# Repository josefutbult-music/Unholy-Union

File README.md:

# Unholy Union
A microphone preamp made for integrating effect pedals to a microphone signal-chain

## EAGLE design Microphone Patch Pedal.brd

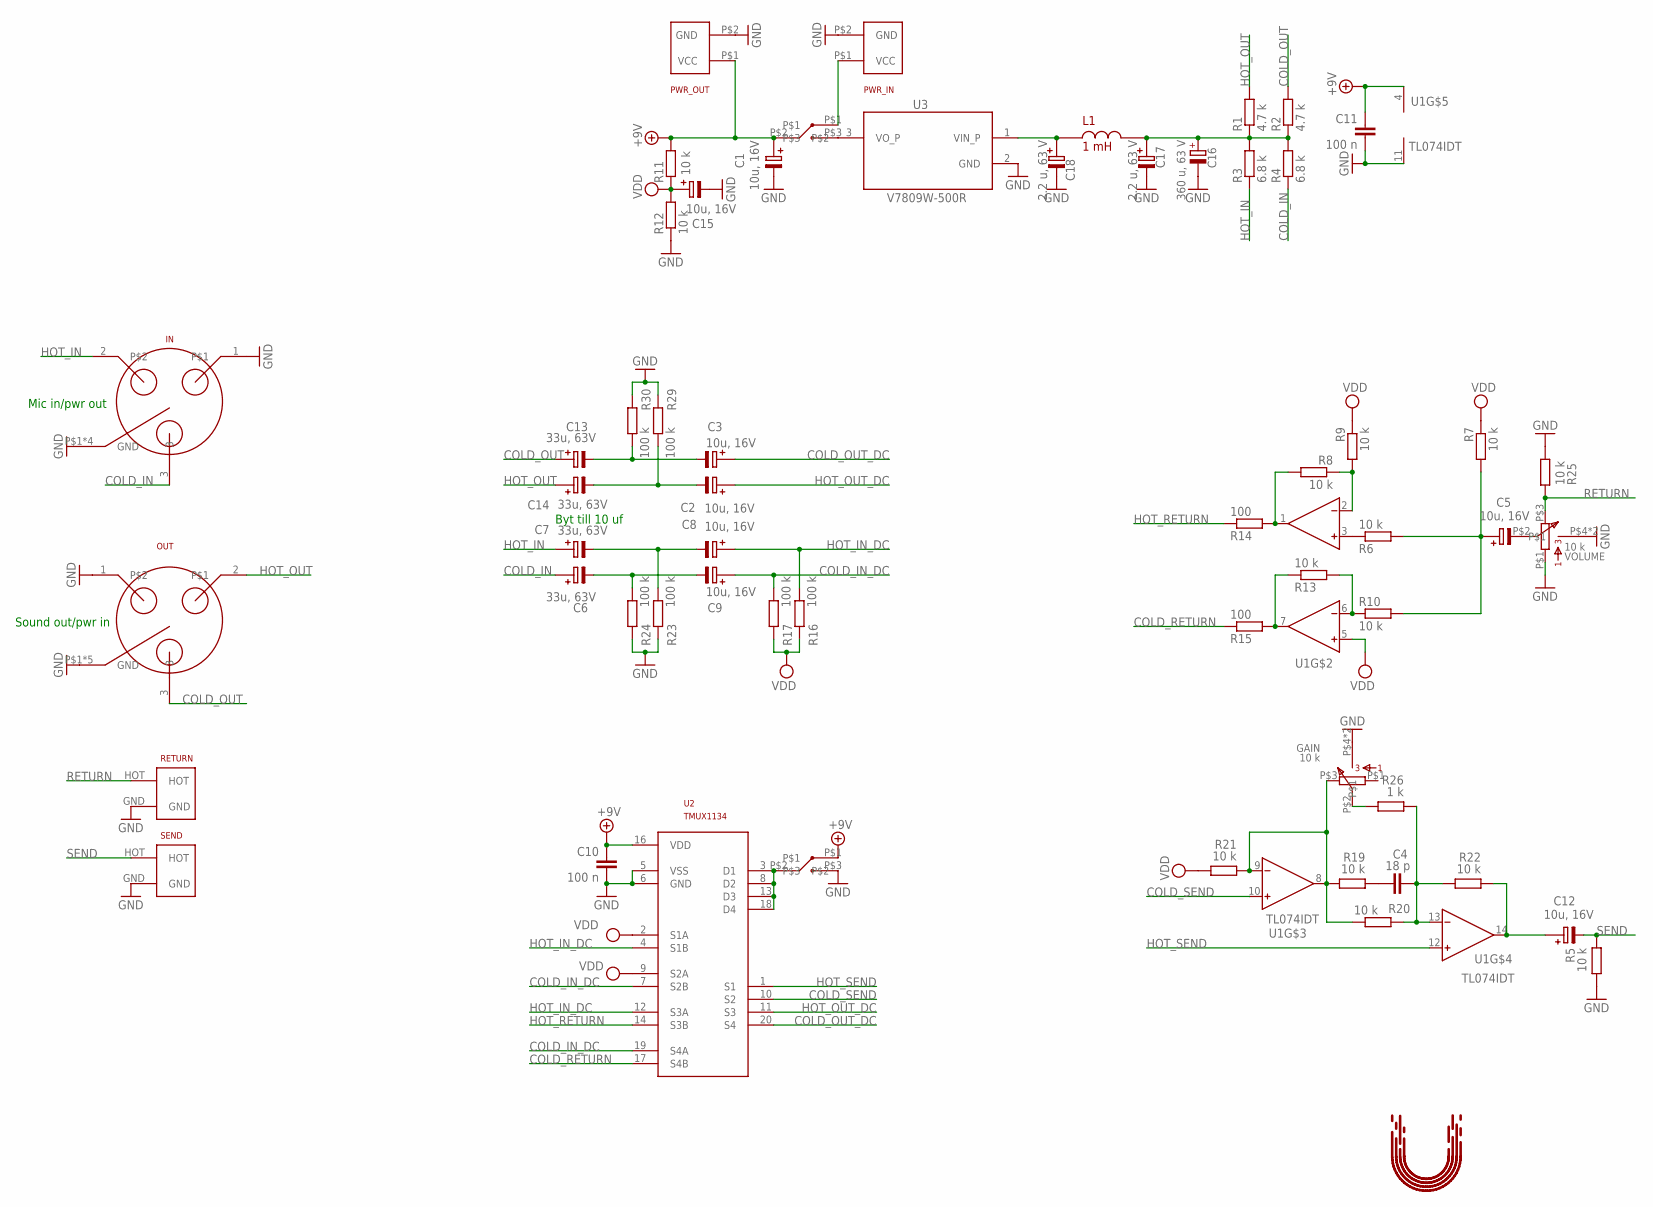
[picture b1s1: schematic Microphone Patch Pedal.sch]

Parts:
BYPASS: BUTTON; 3-HOLES
C1, C2, C3, C5, C8, C9, C12, C15: 10u, 16V; SV-A
C4: 18 p; C0603
C6, C7, C13, C14: 33u, 63V; SV-E/F
C10, C11: 100 n; C0603
C16: 360 u, 63 V; PANASONIC_FK_V_H; MPN UCM1J361MNJ1MS
C17, C18: 2.2 u, 63 V; SV-B; MPN EMVA630ADA2R2MD55G
GAIN: 10 k; RK09L1140
IN: XLR_FEMALE; NC3FAH2-S
L1: 1 mH; R3225
OUT: XLR_MALE; NC3MAH-S
PWR_IN: PWR
PWR_OUT: PWR
R1, R2: 4.7 k; R0603
R3, R4: 6.8 k; R0603
R5, R6, R7, R8, R9, R10, R11, R12, R13, R19, R20, R21, R22, R25: 10 k; R0603
R14, R15: 100; R0603
R16, R17, R23, R24, R29, R30: 100 k; R0603
R26: 1 k; R0603
RETURN: UNBALANCED_INPUT_JACK; BALANCED_INPUT_JACK
SEND: UNBALANCED_INPUT_JACK; BALANCED_INPUT_JACK
SWITCH: BUTTON; 3-HOLES
U1: TL074IDT; SOIC127P600X175-14N
U2: TMUX1134; SOP65P640X120-20N
U3: V7809W-500R; CONV_V7809W-500R
U$1: UTBULT_DESIGN4; UD_4
VOLUME: 10 k; RK09L1140

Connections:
+9V: BYPASS.P$1, C1.+, C10.1, C11.1, PWR_OUT.P$1 (VCC), R11.2, SWITCH.P$2, U1.4 (V+), U2.16 (VDD)
COLD_IN: C6.+, IN.3, R4.1
COLD_IN_DC: C9.+, R17.2, U2.7 (S2B), U2.19 (S4A)
COLD_OUT: C13.+, OUT.3, R2.2
COLD_OUT_DC: C3.+, U2.20 (S4)
COLD_RETURN: R15.1, U2.17 (S4B)
COLD_SEND: U1.10 (IN+), U2.10 (S2)
GND: BYPASS.P$3, C1.-, C10.2, C11.2, C15.-, C16.-, C17.-, C18.-, GAIN.P$4, GAIN.P$5, IN.1, IN.P$1 (GND), IN.P$2 (GND), IN.P$3 (GND), IN.P$6 (GND), OUT.1, OUT.P$1 (GND), OUT.P$2 (GND), OUT.P$3 (GND), OUT.P$4 (GND), OUT.P$5 (GND), PWR_IN.P$2 (GND), PWR_OUT.P$2 (GND), R5.2, R12.1, R23.1, R24.1, R25.2, R29.1, R30.1, RETURN.GND, SEND.GND, U1.11 (V-), U2.5 (VSS), U2.6 (GND), U3.2 (GND), VOLUME.P$1 (1), VOLUME.P$4, VOLUME.P$5
HOT_IN: C7.+, IN.2, R3.1
HOT_IN_DC: C8.+, R16.2, U2.4 (S1B), U2.12 (S3A)
HOT_OUT: C14.+, OUT.2, R1.2
HOT_OUT_DC: C2.+, U2.11 (S3)
HOT_RETURN: R14.1, U2.14 (S3B)
HOT_SEND: U1.12 (IN+), U2.1 (S1)
unnamed: R6.1, U1.3 (IN+)
unnamed: R8.2, R14.2, U1.1 (OUT)
unnamed: R8.1, R9.2, U1.2 (IN-)
unnamed: R10.1, R13.2, U1.6 (IN-)
unnamed: R13.1, R15.2, U1.7 (OUT)
unnamed: C5.-, VOLUME.P$2 (2)
unnamed: C16.+, C17.+, L1.2, R1.1, R2.1, R3.2, R4.2
unnamed: GAIN.P$3 (3), R19.2, R20.2, R21.1, U1.8 (OUT), U1.9 (IN-)
unnamed: SWITCH.P$3, U3.3 (VO_P)
unnamed: C4.1, R19.1
unnamed: C4.2, R20.1, R22.2, R26.1, U1.13 (IN-)
unnamed: C12.+, R22.1, U1.14 (OUT)
unnamed: C7.-, C8.-, R23.2
unnamed: C6.-, C9.-, R24.2
unnamed: C18.+, L1.1, U3.1 (VIN_P)
unnamed: GAIN.P$2 (2), R26.2
unnamed: C2.-, C14.-, R29.2
unnamed: C3.-, C13.-, R30.2
unnamed: C5.+, R6.2, R7.2, R10.2
unnamed: PWR_IN.P$1 (VCC), SWITCH.P$1
RETURN: R25.1, RETURN.HOT, VOLUME.P$3 (3)
SELECTOR: BYPASS.P$2, U2.3 (D1), U2.8 (D2), U2.13 (D3), U2.18 (D4)
SEND: C12.-, R5.1, SEND.HOT
VDD: C15.+, R7.1, R9.1, R11.1, R12.2, R16.1, R17.1, R21.2, U1.5 (IN+), U2.2 (S1A), U2.9 (S2A)

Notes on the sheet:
Mic in/pwr out
Sound out/pwr in
Byt till 10 uf

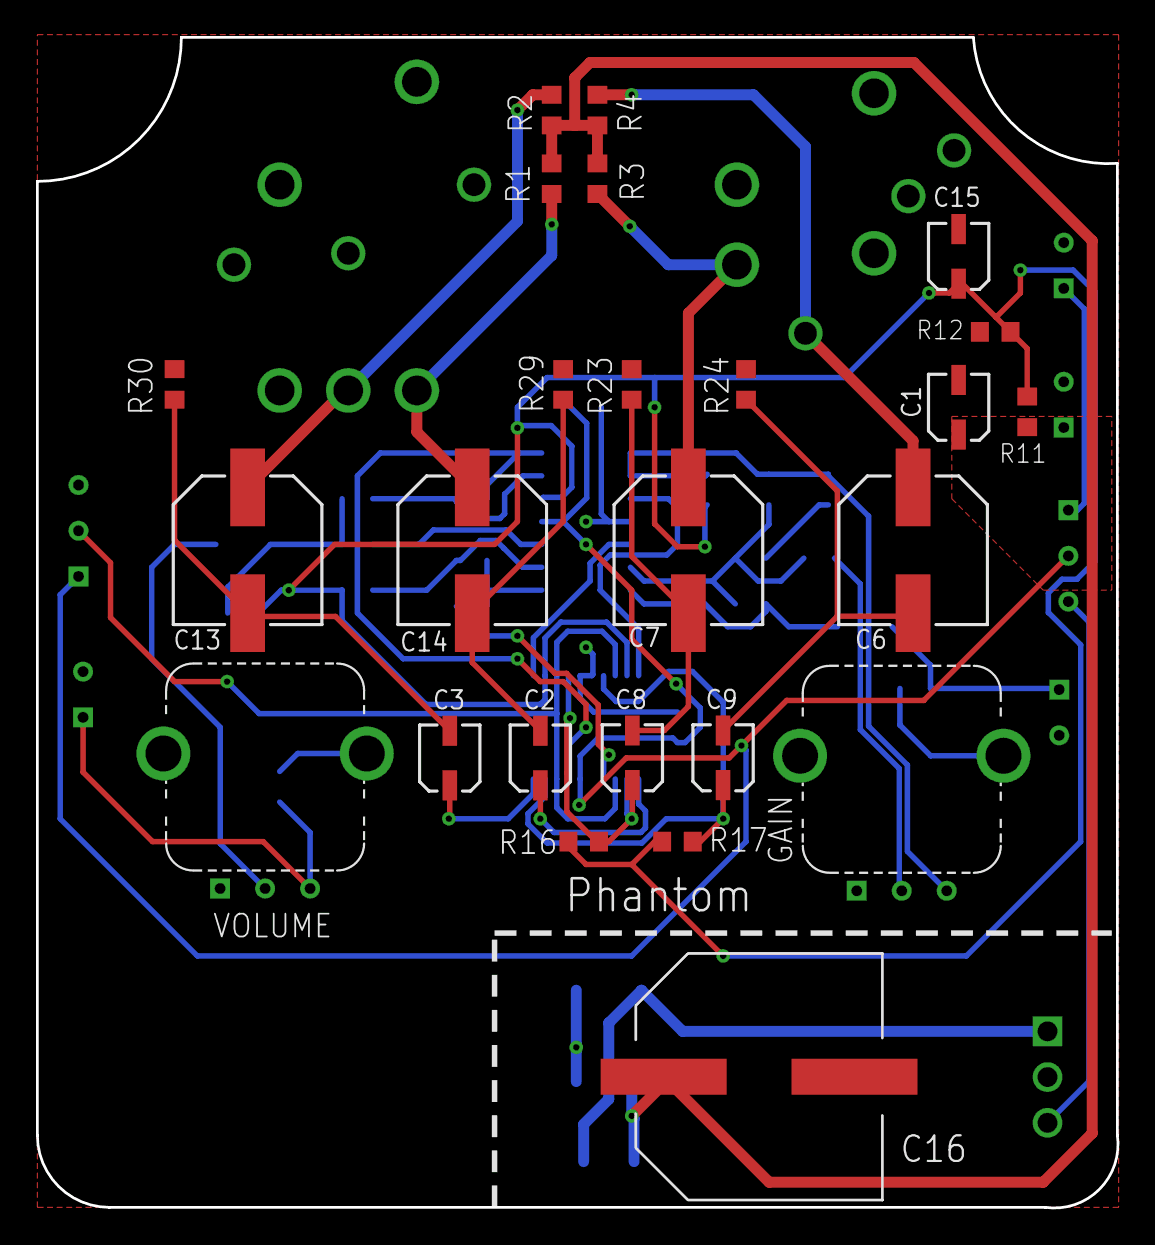
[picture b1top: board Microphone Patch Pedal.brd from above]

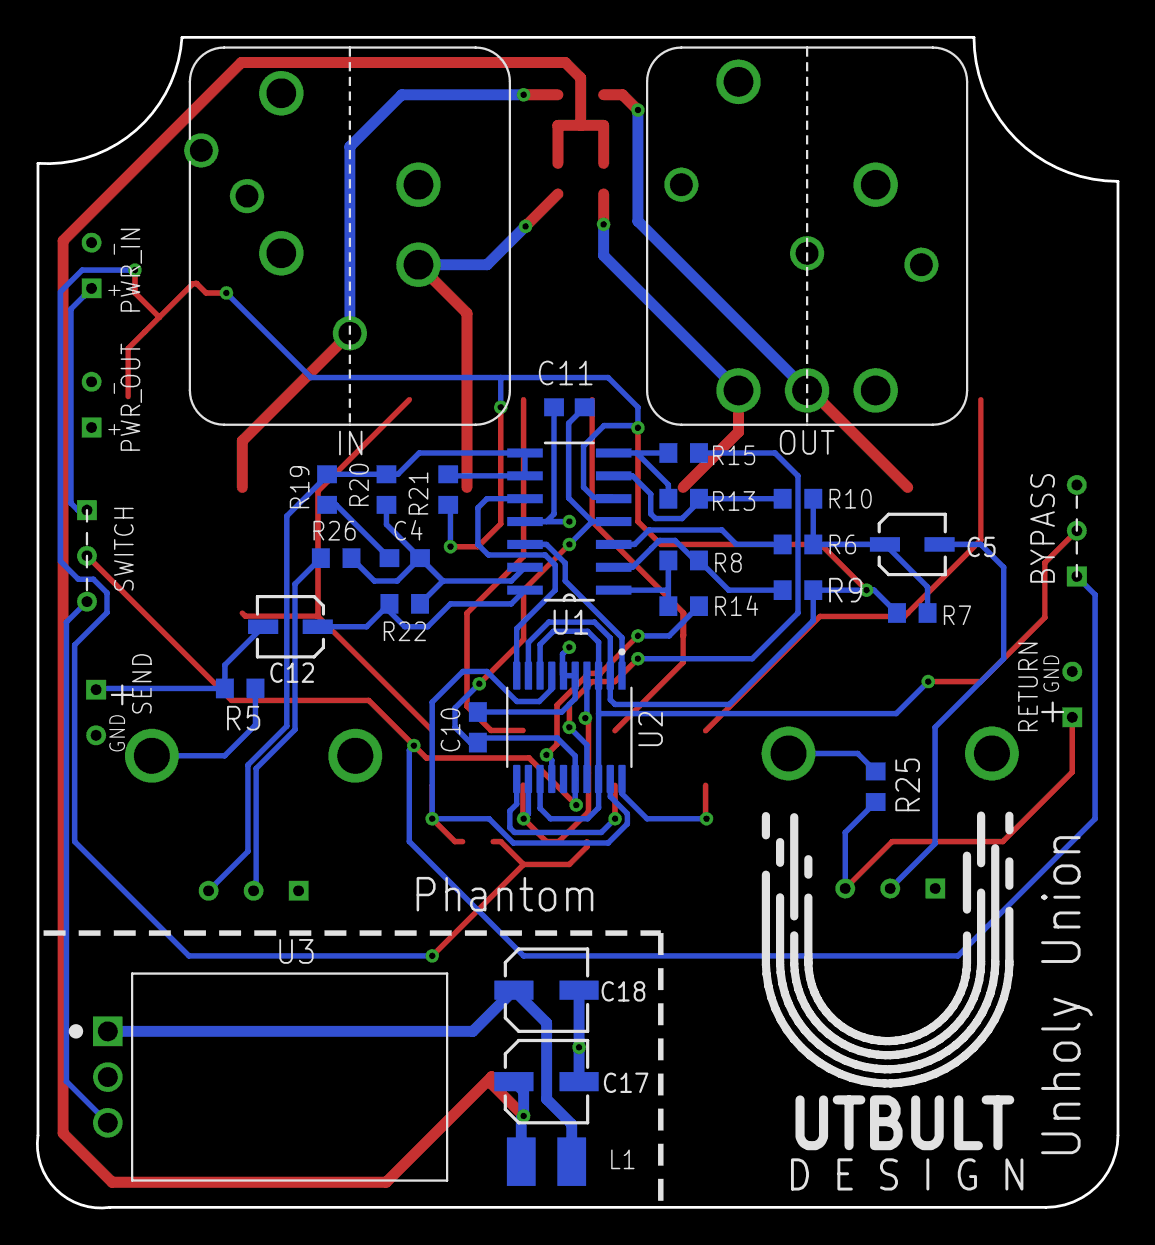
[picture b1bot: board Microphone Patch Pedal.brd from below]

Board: 2 copper layers, 60.0 x 65.0 mm, 60 parts (35 on the bottom side), 38 nets.

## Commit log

2020-10-03 Init
